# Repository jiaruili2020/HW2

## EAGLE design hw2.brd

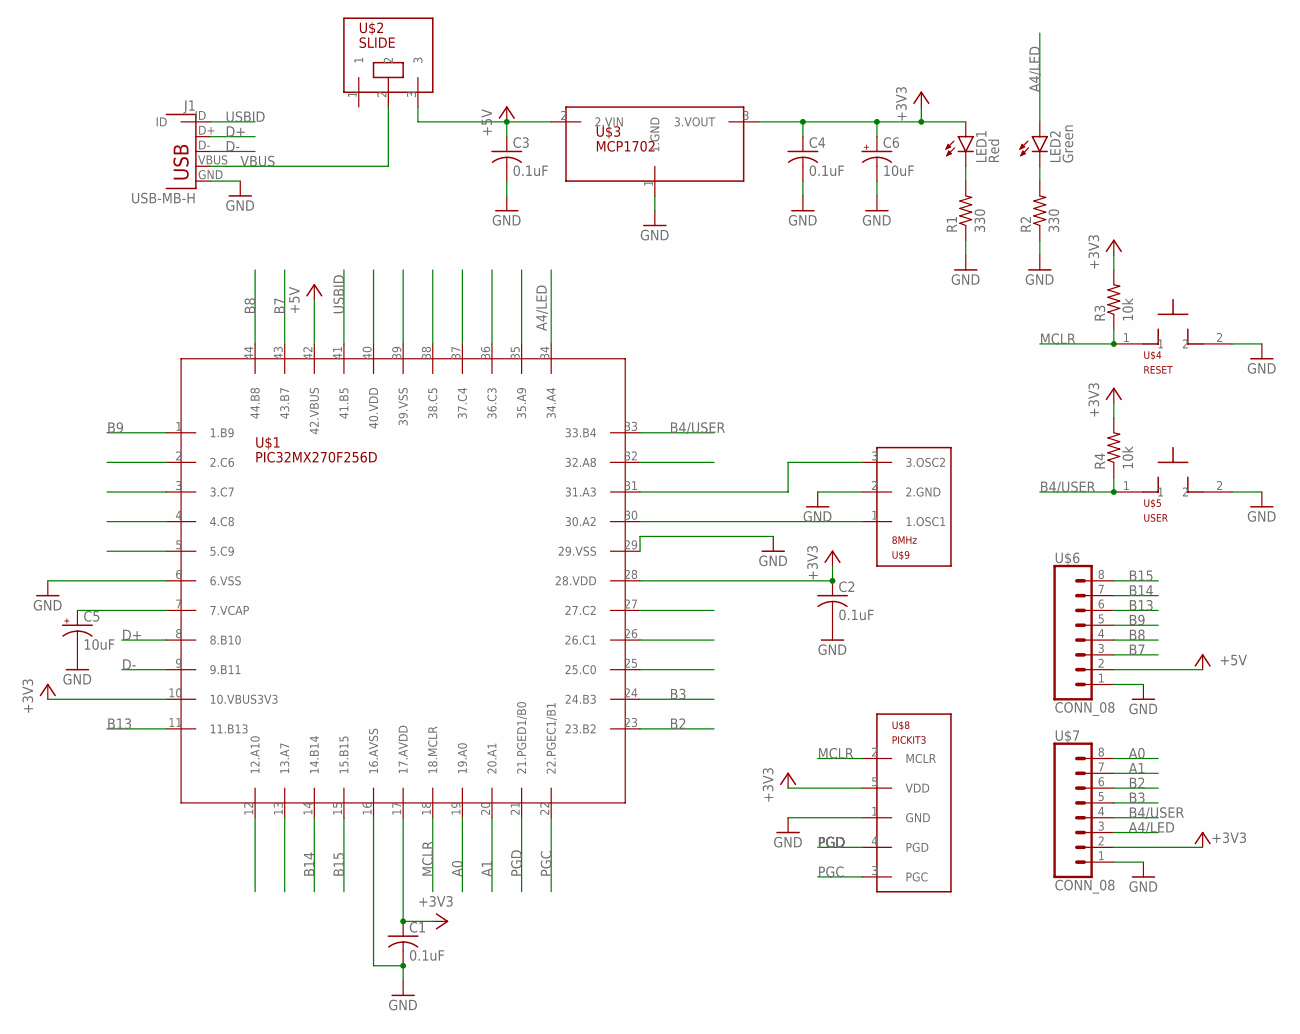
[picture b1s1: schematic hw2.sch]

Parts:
C1, C2, C3, C4: 0.1uF; C025-025X050
C5, C6: 10uF; B45181B
J1: USB-MB-H
LED1: Red; LED3MM
LED2: Green; LED3MM
R1, R2: 330; 0207/10
R3, R4: 10k; 0207/10
U$1: PIC32MX270F256D; TQFP44
U$2: SLIDE
U$3: MCP1702; TO92
U$4: RESET; PB
U$5: USER; PB
U$6, U$7: CONN_08; 1X08
U$8: PICKIT3; 1X05
U$9: 8MHz; OSC

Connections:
+3V3: C1.1, C2.1, C4.1, C6.+, LED1.A, R3.2, R4.2, U$1.10 (10.VBUS3V3), U$1.17 (17.AVDD), U$1.28 (28.VDD), U$3.3 (3.VOUT), U$7.2, U$8.5 (VDD)
+5V: C3.1, U$1.42 (42.VBUS), U$2.3, U$3.2 (2.VIN), U$6.2
A0: U$1.19 (19.A0), U$7.8
A1: U$1.20 (20.A1), U$7.7
A4/LED: LED2.A, U$1.34 (34.A4), U$7.3
B2: U$1.23 (23.B2), U$7.6
B3: U$1.24 (24.B3), U$7.5
B4/USER: R4.1, U$1.33 (33.B4), U$5.1, U$7.4
B7: U$1.43 (43.B7), U$6.3
B8: U$1.44 (44.B8), U$6.4
B9: U$1.1 (1.B9), U$6.5
B13: U$1.11 (11.B13), U$6.6
B14: U$1.14 (14.B14), U$6.7
B15: U$1.15 (15.B15), U$6.8
D+: J1.D+, U$1.8 (8.B10)
D-: J1.D-, U$1.9 (9.B11)
GND: C1.2, C2.2, C3.2, C4.2, C5.-, C6.-, J1.GND, R1.1, R2.1, U$1.6 (6.VSS), U$1.16 (16.AVSS), U$1.29 (29.VSS), U$3.1 (1.GND), U$4.2, U$5.2, U$6.1, U$7.1, U$8.1 (GND), U$9.2 (2.GND)
MCLR: R3.1, U$1.18 (18.MCLR), U$4.1, U$8.2 (MCLR)
unnamed: LED2.K (C), R2.2
unnamed: C5.+, U$1.7 (7.VCAP)
unnamed: LED1.K (C), R1.2
unnamed: U$1.30 (30.A2), U$9.1 (1.OSC1)
unnamed: U$1.31 (31.A3), U$9.3 (3.OSC2)
PGC: U$1.22 (22.PGEC1/B1), U$8.3 (PGC)
PGD: U$1.21 (21.PGED1/B0), U$8.4 (PGD)
USBID: J1.ID, U$1.41 (41.B5)
VBUS: J1.VBUS, U$2.2

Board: 2 copper layers, 22 parts (0 on the bottom side), 27 nets, no tracks yet.
